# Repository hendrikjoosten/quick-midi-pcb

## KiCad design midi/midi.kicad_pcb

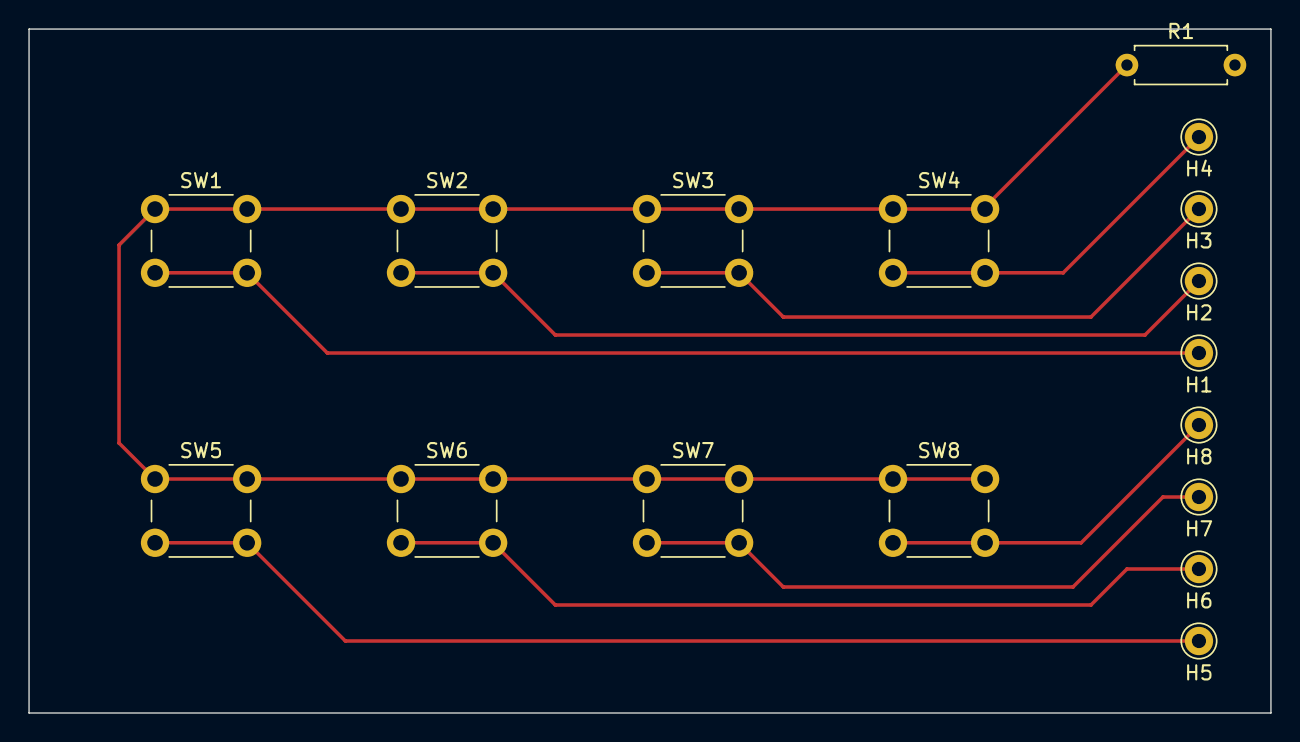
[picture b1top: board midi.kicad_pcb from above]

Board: 2 copper layers, 87.6 x 48.3 mm, 17 parts (0 on the bottom side), 9 nets.

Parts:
H1, H2, H3, H4, H5, H6, H7, H8: MountingHole_Pad; Pin_D1.0mm_L10.0mm
R1: 1M; R_Axial_DIN0207_L6.3mm_D2.5mm_P7.62mm_Horizontal
SW1, SW2, SW3, SW4, SW5, SW6, SW7, SW8: SW_Push_Dual; SW_PUSH_6mm

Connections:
1: H1.1, SW1.2
2: H2.1, SW2.2
3: H3.1, SW3.2
4: H4.1, SW4.2
5: H5.1, SW5.2
6: H6.1, SW6.2
7: H7.1, SW7.2
8: H8.1, SW8.2
VCC: R1.1, SW1.1, SW2.1, SW3.1, SW4.1, SW5.1, SW6.1, SW7.1, SW8.1
